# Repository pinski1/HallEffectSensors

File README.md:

# Hall Effect Sensors

Hall effect sensors for brushless outrunner motors.

This repo contains Hall Effect Sensor PCBs for both internal and external sensors for a few motor diameters.

Many hobby brushless motors do not come with hall effect sensors for position information. By adding one of these boards, aligning it correctly you can pick up the rotation and improve low speed torque of your motor.

These particular ones are designed for 12 slot, 14 pole brushless motors, however the files do contain the formulae to calculate the nessesary spacing for different pole counts.

These versions/copies were inspired by Charles Guan at http://www.etotheipiplusone.net/

## Purchasing

I'm planning to sell these on Tindie at some point.

If you're in the US you may be better served by purchasing from http://e0designs.com/products/hall-effect-sensor-board/

## Parts List

A1221 hall effect sensor
100nF capacitor
ferrite bead
wires
mounting hardware

## Alignment Instructions

1. loosely affix the sensor array in it's mounting point. It will need to be slid sideways to align it.
2. Line up the center sensor with a slot on the stator laminations.
3. Complete.

For a better guide check out: http://e0designs.com/documentation/hall-effect-sensor-board-adapter-installation/ and http://e0designs.com/documentation/finding-motor-phase-sensor-combinations/

# Licence
<br />This work is licensed under a <a rel="license" href="http://creativecommons.org/licenses/by/4.0/">Creative Commons Attribution 4.0 International License</a>.

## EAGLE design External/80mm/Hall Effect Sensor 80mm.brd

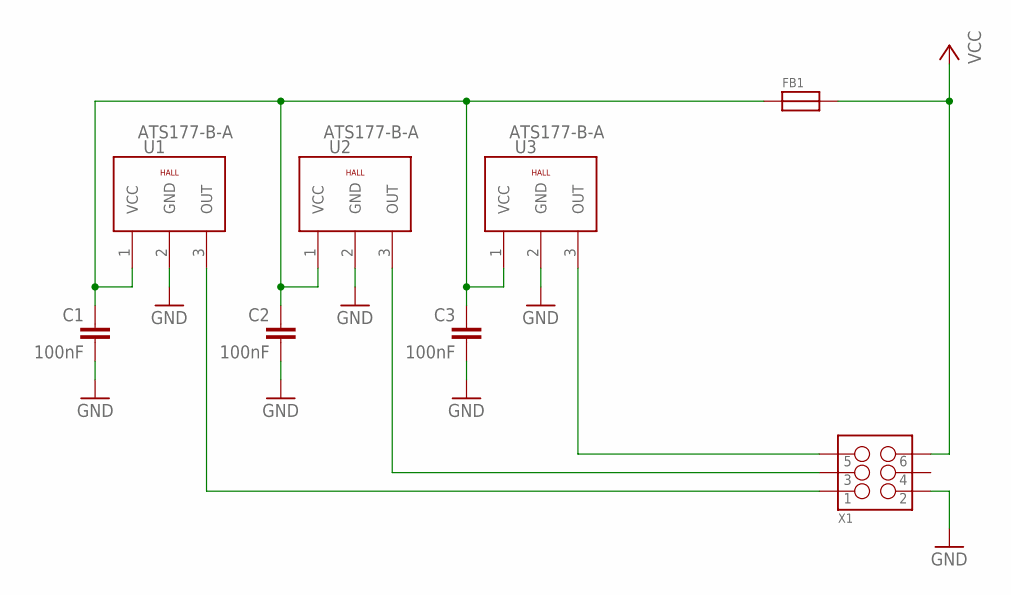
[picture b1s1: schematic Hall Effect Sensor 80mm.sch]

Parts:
C1, C2, C3: 100nF; C0603; MPN CGA3E2X7R1H104K080AA
FB1: FERRITE; 0603; MPN BLM18TG601TN1D
U1, U2, U3: ATS177-B-A; 3PINS1,27; MPN A1221LUA-T
X1: M03X2POGO_PINS; 2X3_POGO

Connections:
GND: C1.2, C2.2, C3.2, U1.2 (GND), U2.2 (GND), U3.2 (GND), X1.P$2 (2)
OUT1: U1.3 (OUT), X1.P$1 (1)
OUT2: U2.3 (OUT), X1.P$3 (3)
OUT3: U3.3 (OUT), X1.P$5 (5)
VCC: FB1.2, X1.P$6 (6)
VDD: C1.1, C2.1, C3.1, FB1.1, U1.1 (VCC), U2.1 (VCC), U3.1 (VCC)

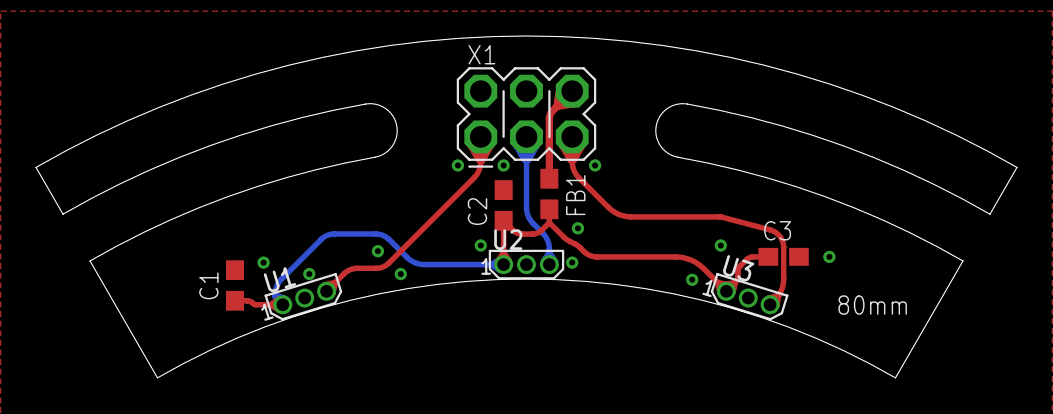
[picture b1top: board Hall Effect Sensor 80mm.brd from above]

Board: 2 copper layers, 54.5 x 19.0 mm, 8 parts (0 on the bottom side), 6 nets.

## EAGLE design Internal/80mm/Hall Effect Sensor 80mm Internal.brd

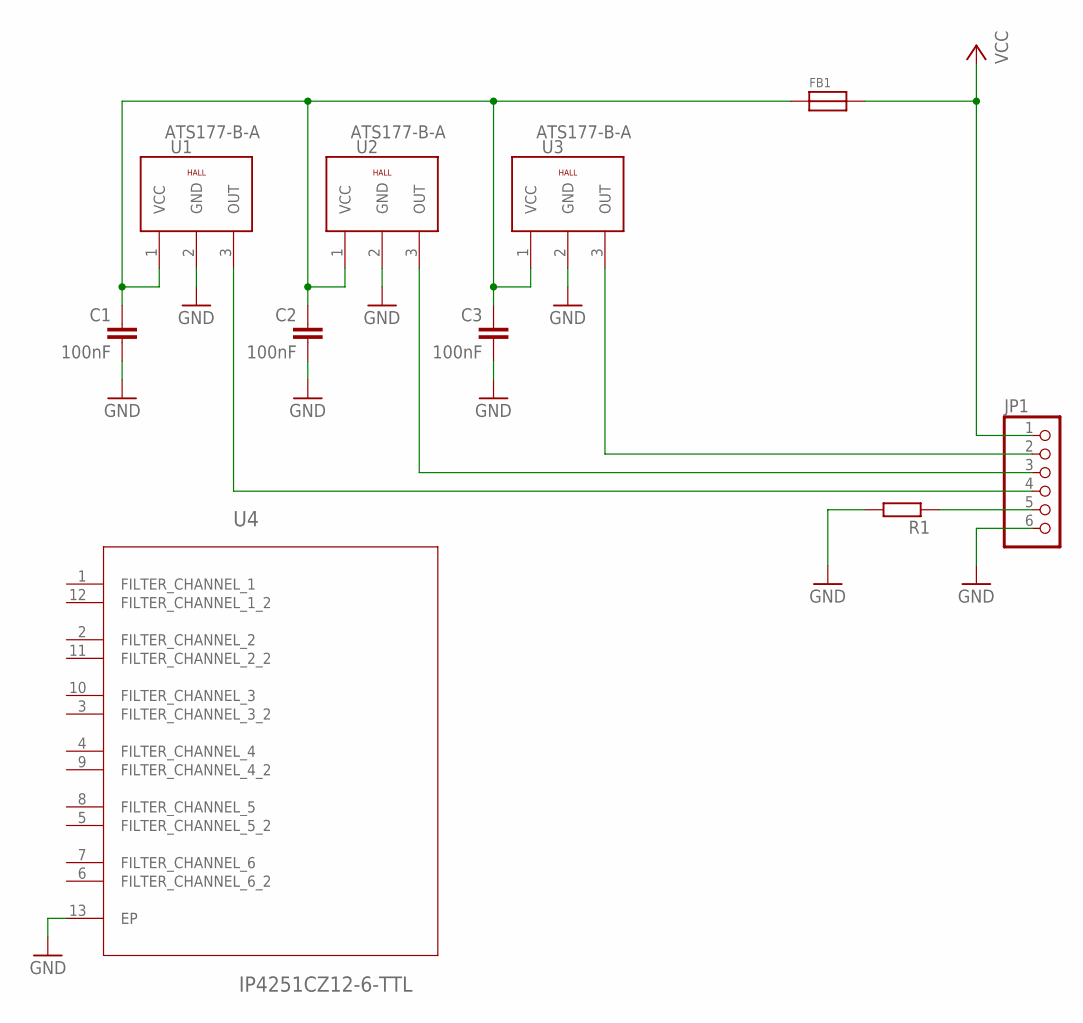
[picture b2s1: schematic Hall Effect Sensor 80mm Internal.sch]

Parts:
C1, C2, C3: 100nF; C0603; MPN CGA3E2X7R1H104K080AA
FB1: FERRITE; 0603; MPN BLM18TG601TN1D
JP1: PINHD-1X6; 1X06
R1: R-EU_R0603; R0603
U1, U2, U3: ATS177-B-A; 3PINS1,27; MPN A1221LUA-T
U4: IP4251CZ12-6-TTL; SON40P135X250X55-13N

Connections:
GND: C1.2, C2.2, C3.2, JP1.6, R1.2, U1.2 (GND), U2.2 (GND), U3.2 (GND), U4.13 (EP)
unnamed: JP1.5, R1.1
OUT1: JP1.4, U1.3 (OUT)
OUT2: JP1.3, U2.3 (OUT)
OUT3: JP1.2, U3.3 (OUT)
VCC: FB1.2, JP1.1
VDD: C1.1, C2.1, C3.1, FB1.1, U1.1 (VCC), U2.1 (VCC), U3.1 (VCC)

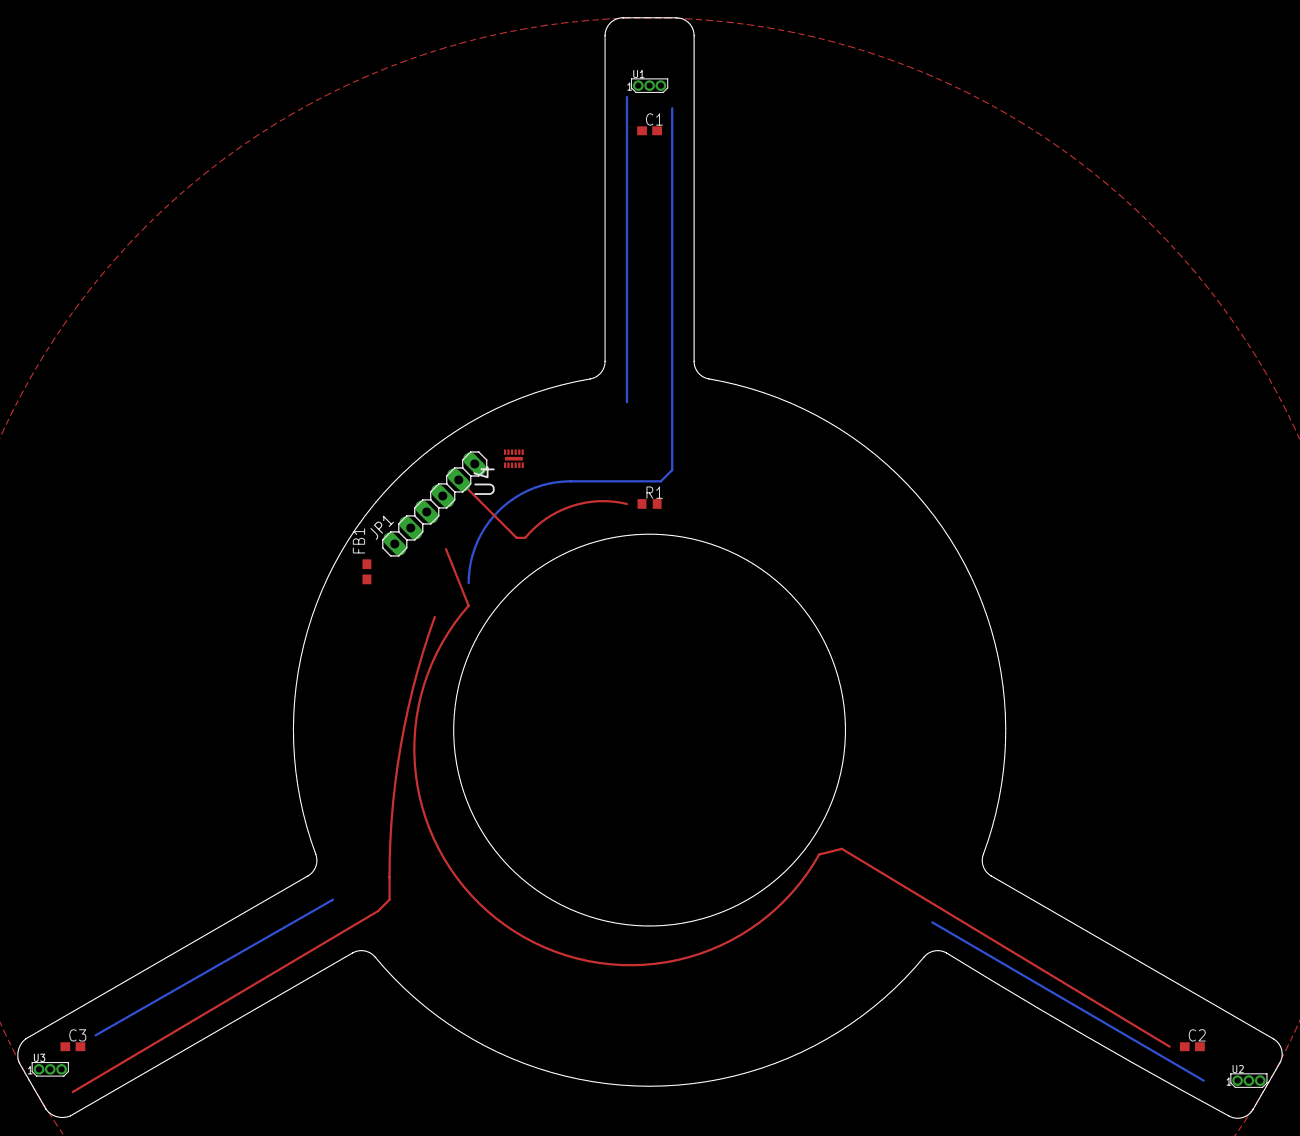
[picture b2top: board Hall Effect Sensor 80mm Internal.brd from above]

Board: 2 copper layers, 142.0 x 123.6 mm, 10 parts (0 on the bottom side), 7 nets.

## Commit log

2017-05-23 Adding HW files & adding to gitignore
2017-05-23 bit more info in the readme
2017-12-01 Adding output files

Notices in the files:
README.md:
License: CC BY 4.0
parts and their libraries:
SparkFun-Connectors: Licensing: Creative Commons ShareAlike 4.0 International - https://creativecommons.org/licenses/by-sa/4.0
